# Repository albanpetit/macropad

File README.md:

# Makerpad

A fully open-source macropad built from scratch — custom PCB, 3D-printed enclosure, and embedded firmware. 20 programmable keys, two rotary encoders, a 2" color display driven by LVGL, and 22 addressable RGB LEDs, all running on an RP2040.

Everything is designed to be reproducible: order the PCB, print the case, flash the firmware, and configure your keymap via a JSON file.

---

## What's inside

| Directory | Description |
|---|---|
| [`ecad/`](ecad/README.md) | KiCad schematic + PCB, BOM, custom footprints |
| [`mcad/`](mcad/README.md) | STEP files for the enclosure |
| [`fw/`](fw/README.md) | PlatformIO firmware (C++, RP2040) |
| `doc/` | Datasheets, iBOM, schematic PDF |

---

## Hardware at a glance

| Component | Part |
|---|---|
| MCU | RP2040 (LQFN-56), 133 MHz, 264 KB RAM |
| Flash | W25Q128JVP — 16 MB SPI |
| Display | HS20HS072RX — 2" 240×320 ST7789V2-HSD SPI |
| RGB LEDs | WS2812B-2020 × 22 — addressable, 5V |
| Keys | 4 cols × 5 rows = 20 keys |
| Encoders | PEC12R-4225F-S0024 × 2 — 24 PPR + push |
| Connectivity | USB-C (HID keyboard + consumer control) |

---

## Roadmap

- [x] Layer switching via encoder
- [x] Volume control with speaker/mic toggle
- [ ] Macro sequence support
- [ ] Per-key LED color from config
- [ ] OTA config update via USB mass storage

---

## Contributing

See [CONTRIBUTING.md](CONTRIBUTING.md) for the commit convention, scope definitions, and contribution guidelines.

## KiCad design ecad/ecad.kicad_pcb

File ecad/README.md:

# ECAD

PCB design for the Makerpad — schematic and layout done in [KiCad](https://www.kicad.org/).

---

## Files

| File / Directory | Description |
|---|---|
| `ecad.kicad_pro` | KiCad project root |
| `ecad.kicad_sch` | Top-level schematic |
| `switches.kicad_sch` | Key matrix sub-sheet |
| `leds.kicad_sch` | LED chain sub-sheet |
| `ecad.kicad_pcb` | PCB layout |
| `library.pretty/` | Custom footprints (RP2040, WS2812B-2020, encoders…) |
| `3d-models/` | STEP files for 3D preview |
| `ecad-backups/` | KiCad auto-backups |

Exported outputs live in `doc/`:

| Output | Description |
|---|---|
| `doc/bom.xlsx` / `bom.pdf` | Bill of materials |
| `doc/schematic.pdf` | Full schematic PDF |
| `doc/ibom/ibom.html` | Interactive BOM (open in browser) |
| `doc/ecad-export/` | Gerbers and drill files |
| `doc/datasheet/` | Datasheets for key components |

---

## Opening the project

```bash
kicad ecad.kicad_pro
```

Requires KiCad 8 or later. All symbols and footprints are embedded or resolved via `sym-lib-table` and `fp-lib-table` — no external library setup needed.

---

## Interactive BOM

Open `doc/ibom/ibom.html` in any browser. Click a component to highlight its position on the board — useful when soldering.

---

## Ordering the PCB

1. Use the Gerbers in `doc/ecad-export/` and upload them to your preferred fabricator (JLCPCB, PCBWay, OSHPark…).
2. Recommended specs: 2-layer, 1.6 mm FR4, HASL or ENIG finish, 0.2 mm min trace/space.
3. Cross-reference the BOM (`doc/bom.xlsx`) for part numbers and quantities.

---

## Custom footprints (`library.pretty/`)

| Footprint | Component |
|---|---|
| `QFN-56-1EP_7x7mm_P0.4mm` | RP2040 |
| `LED_WS2812B-2020_PLCC4_2.0x2.0mm` | WS2812B-2020 RGB LED |
| `Crystal_SMD_Abracon_ABM8G-4Pin_3.2x2.5mm` | 12 MHz crystal |
| `Hirose_FH12-12S-0.5SH` | 0.5 mm FPC connector (display) |
| `PinHeader_2x05_P1.27mm_Vertical_SMD` | SWD debug header |

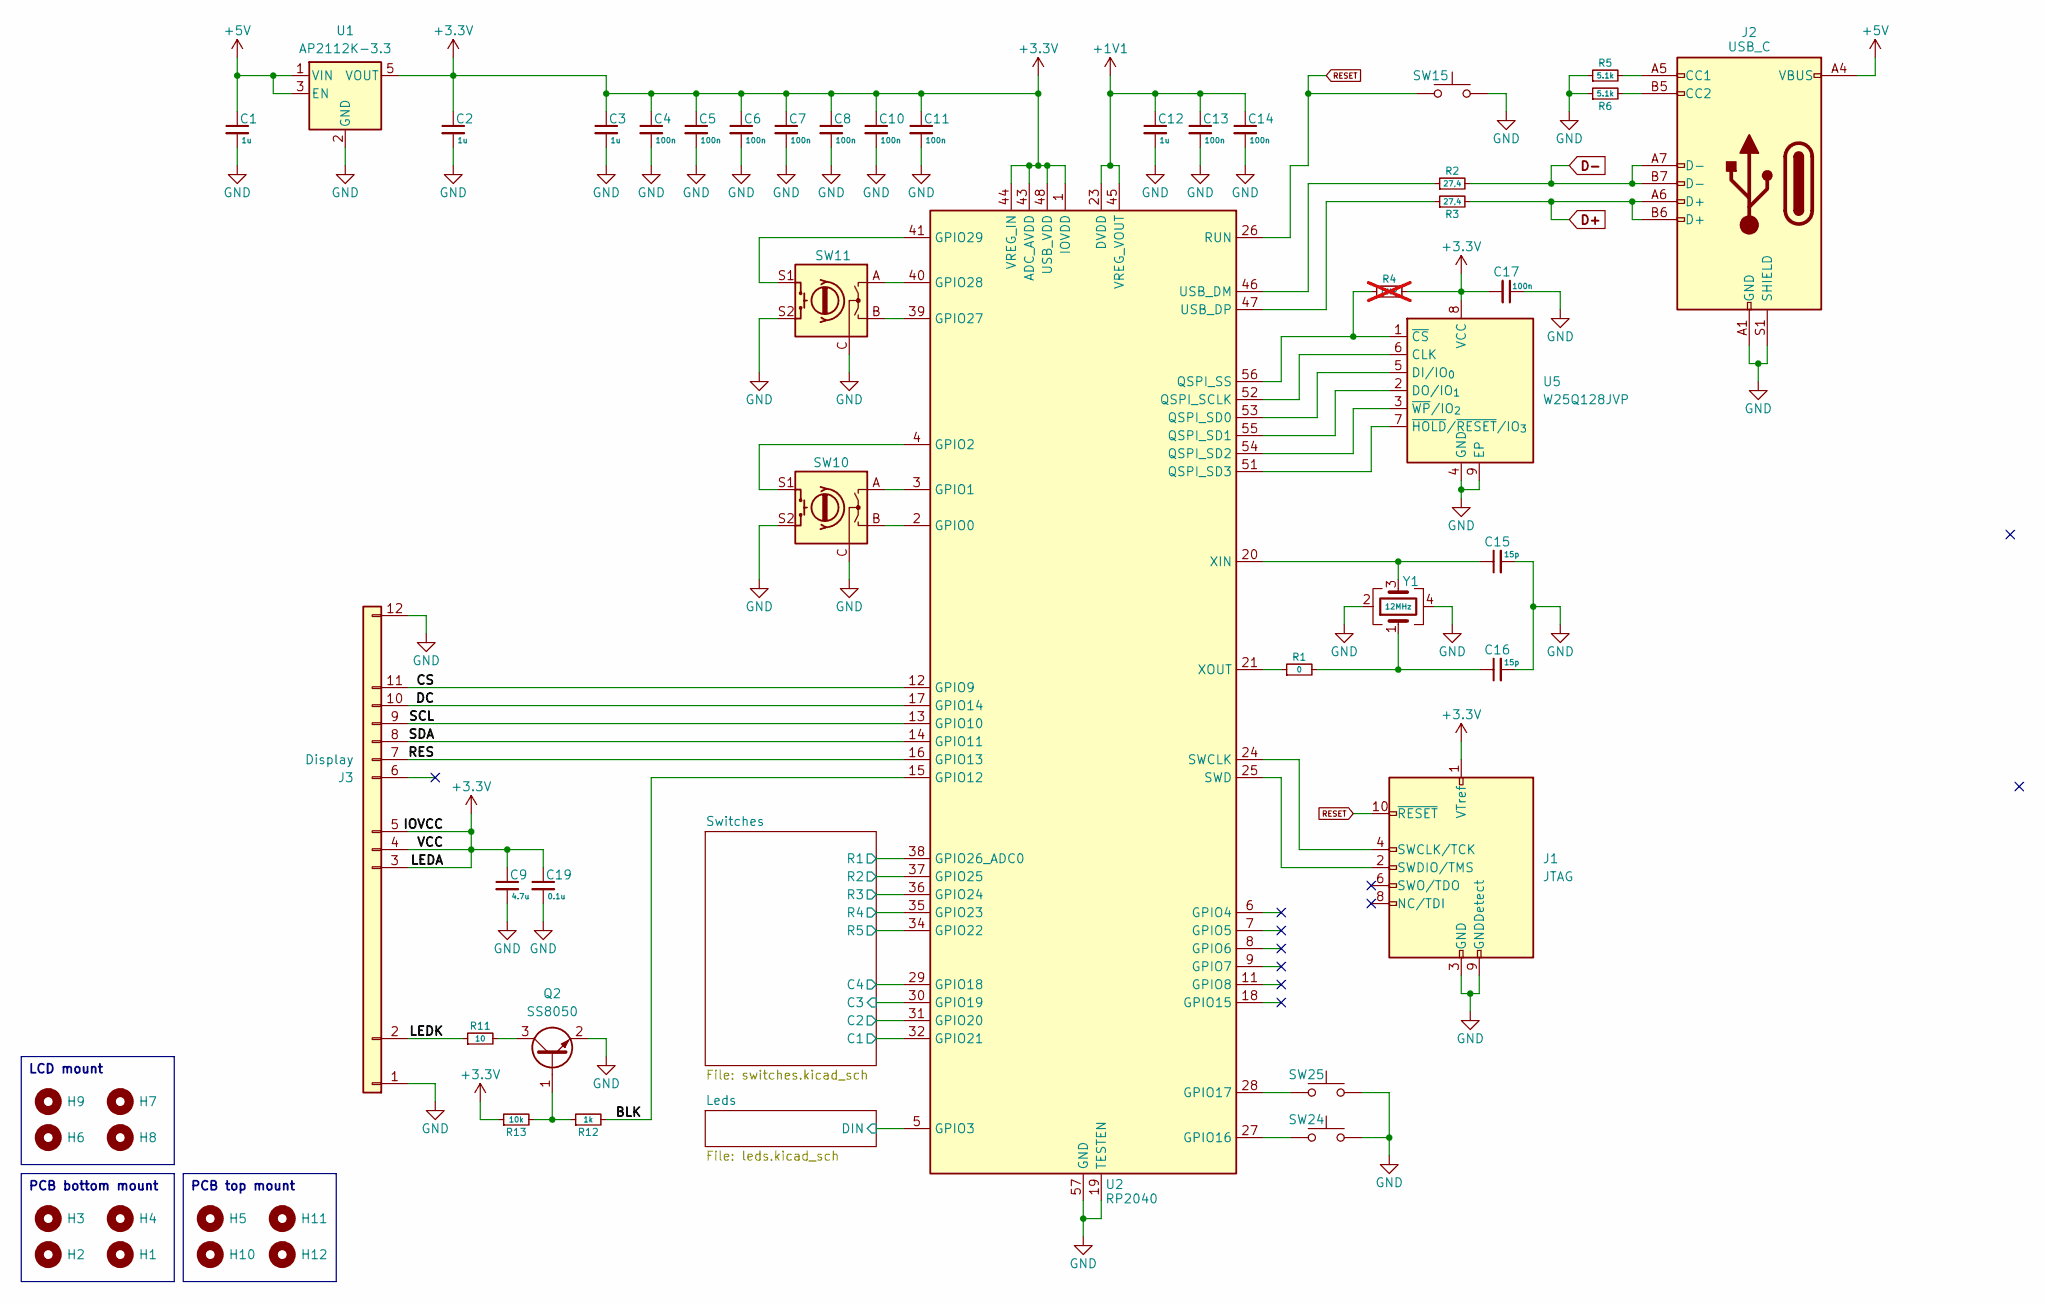
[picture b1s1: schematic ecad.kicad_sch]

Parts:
C1, C2, C3, C12: 1u; C_0402_1005Metric
C4, C5, C6, C7, C8, C10, C11, C13, C14, C17: 100n; C_0402_1005Metric
C9: 4.7u; C_0402_1005Metric
C15, C16: 15p; C_0402_1005Metric
C19: 0.1u; C_0402_1005Metric
H1, H2, H3, H4: MountingHole; smtso3030ctj
H5, H10, H11, H12: MountingHole; MountingHole_3.2mm_M3_DIN965
H6, H7, H8, H9: MountingHole; MountingHole_2.2mm_M2_DIN965
J1: JTAG; PinHeader_2x05_P1.27mm_Vertical_SMD
J2: USB_C; USB_C_Receptacle_Amphenol_12401948E412A
J3: Display; Hirose_FH12-12S-0.5SH_1x12-1MP_P0.50mm_Horizontal
Q2: SS8050; SOT-23
R1: 0; R_0402_1005Metric
R2, R3: 27,4; R_0402_1005Metric
R4: DNP; R_0402_1005Metric; not fitted
R5, R6: 5.1k; R_0402_1005Metric
R11: 10; R_0402_1005Metric
R12: 1k; R_0402_1005Metric
R13: 10k; R_0402_1005Metric
SW10, SW11: RotaryEncoder_Switch; RotaryEncoder_Bourns_Vertical_PEC12R-3x17F-Sxxxx
SW15: RESET; SW_Push_1P1T_NO_CK_KMR2
SW24, SW25: SW_PUSH_6mm
U1: AP2112K-3.3; SOT-23-5
U2: RP2040; QFN-56-1EP_7x7mm_P0.4mm_EP3.2x3.2mm
U5: W25Q128JVP; WSON-8-1EP_6x5mm_P1.27mm_EP3.4x4.3mm
Y1: 12MHz; Crystal_SMD_Abracon_ABM8G-4Pin_3.2x2.5mm

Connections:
+1V1: C12.1, C13.1, C14.1, U2.23 (DVDD), U2.45 (VREG_VOUT), U2.50 (DVDD)
+3.3V: C2.1, C3.1, C4.1, C5.1, C6.1, C7.1, C8.1, C9.1, C10.1, C11.1, C17.2, C19.1, J1.1 (VTref), J3.3, J3.4, J3.5, R4.2, R13.1, U1.5 (VOUT), U2.1 (IOVDD), U2.10 (IOVDD), U2.22 (IOVDD), U2.33 (IOVDD), U2.42 (IOVDD), U2.43 (ADC_AVDD), U2.44 (VREG_IN), U2.48 (USB_VDD), U2.49 (IOVDD), U5.8 (VCC)
+5V: C1.1, J2.A4 (VBUS), J2.A9 (VBUS), J2.B4 (VBUS), J2.B9 (VBUS), U1.1 (VIN), U1.3 (EN); also elsewhere on the board
/BLK: R12.2, U2.15 (GPIO12)
/CS: J3.11, U2.12 (GPIO9)
/DC: J3.10, U2.17 (GPIO14)
/LEDK: J3.2, R11.1
/Leds/DIN: U2.5 (GPIO3); also elsewhere on the board
/RES: J3.7, U2.16 (GPIO13)
/SCL: J3.9, U2.13 (GPIO10)
/SDA: J3.8, U2.14 (GPIO11)
/Switches/C1: U2.32 (GPIO21); also elsewhere on the board
/Switches/C2: U2.31 (GPIO20); also elsewhere on the board
/Switches/C3: U2.30 (GPIO19); also elsewhere on the board
/Switches/C4: U2.29 (GPIO18); also elsewhere on the board
/Switches/R1: U2.38 (GPIO26_ADC0); also elsewhere on the board
/Switches/R2: U2.37 (GPIO25); also elsewhere on the board
/Switches/R3: U2.36 (GPIO24); also elsewhere on the board
/Switches/R4: U2.35 (GPIO23); also elsewhere on the board
/Switches/R5: U2.34 (GPIO22); also elsewhere on the board
D+: J2.A6 (D+), J2.B6 (D+), R3.2
D-: J2.A7 (D-), J2.B7 (D-), R2.2
GND: C1.2, C2.2, C3.2, C4.2, C5.2, C6.2, C7.2, C8.2, C9.2, C10.2, C11.2, C12.2, C13.2, C14.2, C15.2, C16.2, C17.1, C19.2, J1.3 (GND), J1.5 (GND), J1.9 (GNDDetect), J2.A1 (GND), J2.A12 (GND), J2.B1 (GND), J2.B12 (GND), J2.S1 (SHIELD), J3.1, J3.12, Q2.2 (E), R5.1, R6.1, SW10.C, SW10.S2, SW11.C, SW11.S2, SW15.2, SW24.2, SW25.2, U1.2 (GND), U2.19 (TESTEN), U2.57 (GND), U5.4 (GND), U5.9 (EP), Y1.2, Y1.4; also elsewhere on the board
unnamed: C16.1, R1.2, Y1.1
unnamed: J1.4 (SWCLK/TCK), U2.24 (SWCLK)
unnamed: J1.2 (SWDIO/TMS), U2.25 (SWD)
unnamed: J2.A5 (CC1), R5.2
unnamed: J2.B5 (CC2), R6.2
unnamed: Q2.1 (B), R12.1, R13.2
unnamed: Q2.3 (C), R11.2
unnamed: SW10.B, U2.2 (GPIO0)
unnamed: SW10.A, U2.3 (GPIO1)
unnamed: SW10.S1, U2.4 (GPIO2)
unnamed: SW24.1, U2.27 (GPIO16)
unnamed: SW25.1, U2.28 (GPIO17)
unnamed: SW11.B, U2.39 (GPIO27)
unnamed: SW11.A, U2.40 (GPIO28)
unnamed: SW11.S1, U2.41 (GPIO29)
unnamed: U2.52 (QSPI_SCLK), U5.6 (CLK)
unnamed: U2.53 (QSPI_SD0), U5.5 (DI/IO_{0})
unnamed: U2.55 (QSPI_SD1), U5.2 (DO/IO_{1})
unnamed: U2.54 (QSPI_SD2), U5.3 (~WP/IO_{2})
unnamed: U2.51 (QSPI_SD3), U5.7 (~HOLD/~RESET/IO_{3})
unnamed: R4.1, U2.56 (QSPI_SS), U5.1 (~CS)
unnamed: R2.1, U2.46 (USB_DM)
unnamed: R3.1, U2.47 (USB_DP)
unnamed: C15.1, U2.20 (XIN), Y1.3
unnamed: R1.1, U2.21 (XOUT)
RESET: J1.10 (~RESET), SW15.1, U2.26 (RUN)

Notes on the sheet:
LCD mount
PCB bottom mount
PCB top mount

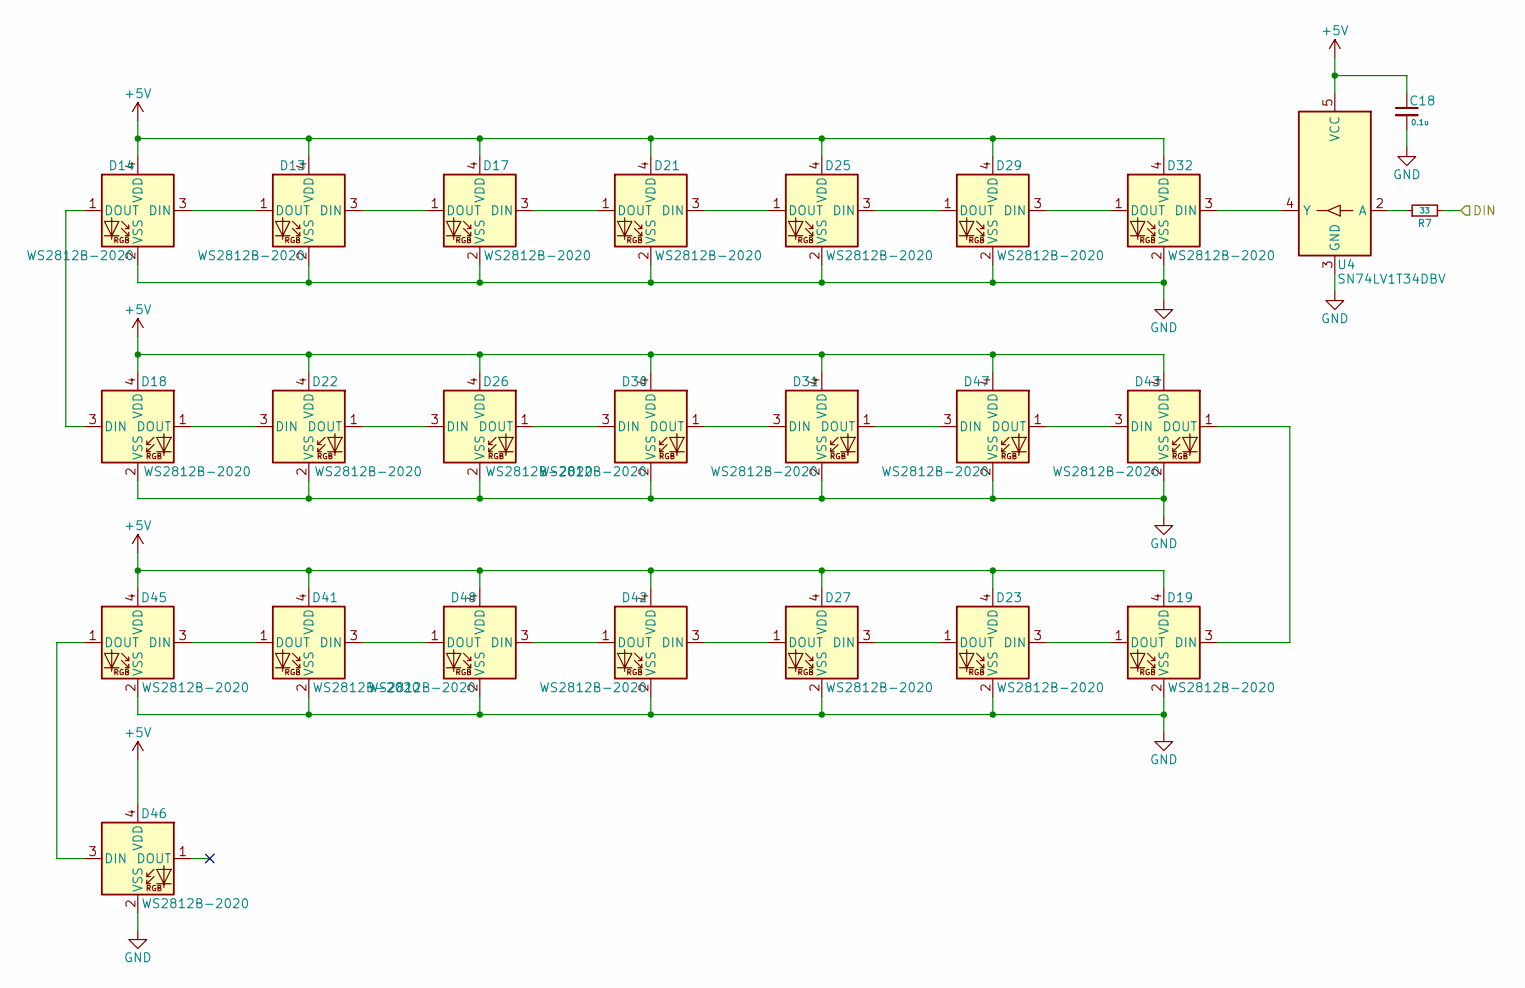
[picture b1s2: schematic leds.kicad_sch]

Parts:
C18: 0.1u; C_0402_1005Metric
D13, D14, D17, D18, D19, D21, D22, D23, D25, D26, D27, D29, D30, D31, D32, D41, D42, D43, D45, D46, D47, D48: WS2812B-2020; LED_WS2812B-2020_PLCC4_2.0x2.0mm
R7: 33; R_0402_1005Metric
U4: SN74LV1T34DBV; SOT-23-5

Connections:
+5V: C18.1, D13.4 (VDD), D14.4 (VDD), D17.4 (VDD), D18.4 (VDD), D19.4 (VDD), D21.4 (VDD), D22.4 (VDD), D23.4 (VDD), D25.4 (VDD), D26.4 (VDD), D27.4 (VDD), D29.4 (VDD), D30.4 (VDD), D31.4 (VDD), D32.4 (VDD), D41.4 (VDD), D42.4 (VDD), D43.4 (VDD), D45.4 (VDD), D46.4 (VDD), D47.4 (VDD), D48.4 (VDD), U4.5 (VCC); also elsewhere on the board
/Leds/DIN: R7.2; also elsewhere on the board
GND: C18.2, D13.2 (VSS), D14.2 (VSS), D17.2 (VSS), D18.2 (VSS), D19.2 (VSS), D21.2 (VSS), D22.2 (VSS), D23.2 (VSS), D25.2 (VSS), D26.2 (VSS), D27.2 (VSS), D29.2 (VSS), D30.2 (VSS), D31.2 (VSS), D32.2 (VSS), D41.2 (VSS), D42.2 (VSS), D43.2 (VSS), D45.2 (VSS), D46.2 (VSS), D47.2 (VSS), D48.2 (VSS), U4.3 (GND); also elsewhere on the board
unnamed: D13.3 (DIN), D17.1 (DOUT)
unnamed: D13.1 (DOUT), D14.3 (DIN)
unnamed: D14.1 (DOUT), D18.3 (DIN)
unnamed: D17.3 (DIN), D21.1 (DOUT)
unnamed: D18.1 (DOUT), D22.3 (DIN)
unnamed: D19.3 (DIN), D43.1 (DOUT)
unnamed: D19.1 (DOUT), D23.3 (DIN)
unnamed: D21.3 (DIN), D25.1 (DOUT)
unnamed: D22.1 (DOUT), D26.3 (DIN)
unnamed: D23.1 (DOUT), D27.3 (DIN)
unnamed: D25.3 (DIN), D29.1 (DOUT)
unnamed: D26.1 (DOUT), D30.3 (DIN)
unnamed: D27.1 (DOUT), D42.3 (DIN)
unnamed: D29.3 (DIN), D32.1 (DOUT)
unnamed: D30.1 (DOUT), D31.3 (DIN)
unnamed: D31.1 (DOUT), D47.3 (DIN)
unnamed: D32.3 (DIN), U4.4 (Y)
unnamed: D41.3 (DIN), D48.1 (DOUT)
unnamed: D41.1 (DOUT), D45.3 (DIN)
unnamed: D42.1 (DOUT), D48.3 (DIN)
unnamed: D43.3 (DIN), D47.1 (DOUT)
unnamed: D45.1 (DOUT), D46.3 (DIN)
unnamed: R7.1, U4.2 (A)

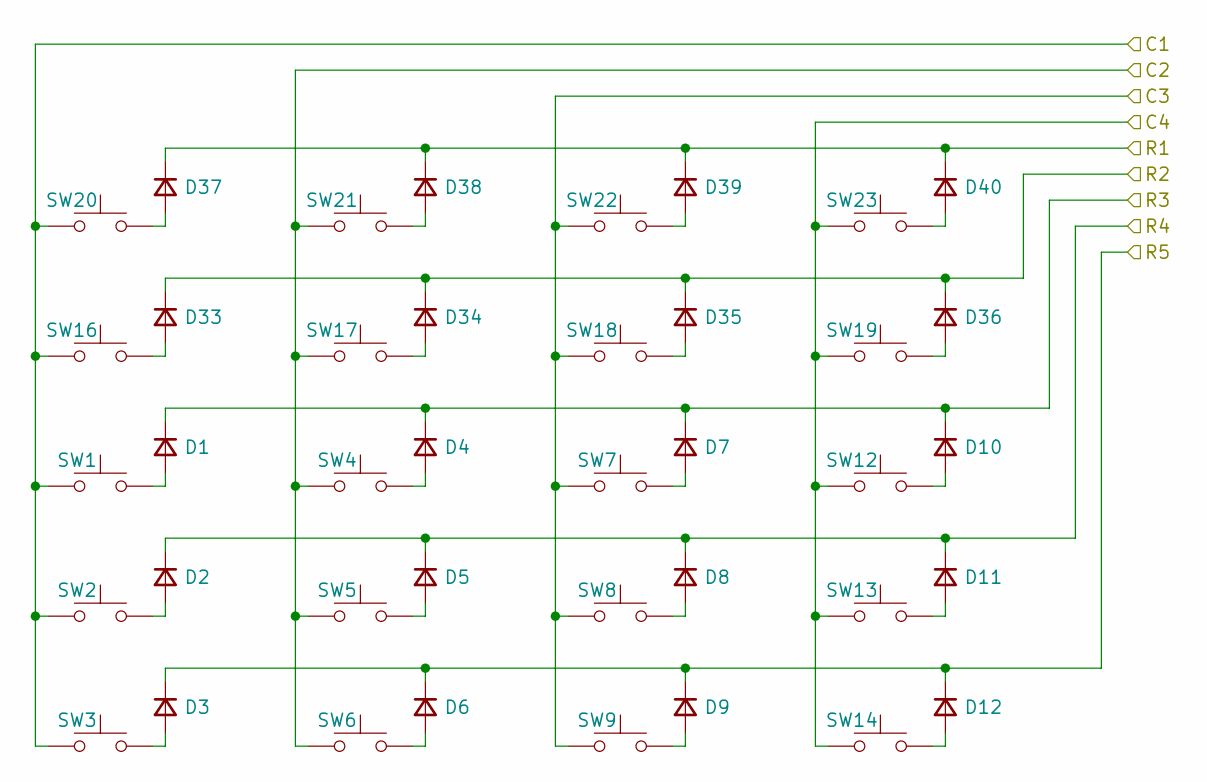
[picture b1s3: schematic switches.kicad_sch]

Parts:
D1, D2, D3, D4, D5, D6, D7, D8, D9, D10, D11, D12, D33, D34, D35, D36, D37, D38, D39, D40: 1N4148W; D_SOD-123
SW1, SW2, SW3, SW4, SW5, SW6, SW7, SW8, SW9, SW12, SW13, SW14, SW16, SW17, SW18, SW19, SW20, SW21, SW22, SW23: Kailh choc v2; SW_Hotswap_Kailh_Choc_V2

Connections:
/Switches/C1: SW1.1, SW2.1, SW3.1, SW16.1, SW20.1; also elsewhere on the board
/Switches/C2: SW4.1, SW5.1, SW6.1, SW17.1, SW21.1; also elsewhere on the board
/Switches/C3: SW7.1, SW8.1, SW9.1, SW18.1, SW22.1; also elsewhere on the board
/Switches/C4: SW12.1, SW13.1, SW14.1, SW19.1, SW23.1; also elsewhere on the board
/Switches/R1: D37.1 (K), D38.1 (K), D39.1 (K), D40.1 (K); also elsewhere on the board
/Switches/R2: D33.1 (K), D34.1 (K), D35.1 (K), D36.1 (K); also elsewhere on the board
/Switches/R3: D1.1 (K), D4.1 (K), D7.1 (K), D10.1 (K); also elsewhere on the board
/Switches/R4: D2.1 (K), D5.1 (K), D8.1 (K), D11.1 (K); also elsewhere on the board
/Switches/R5: D3.1 (K), D6.1 (K), D9.1 (K), D12.1 (K); also elsewhere on the board
unnamed: D1.2 (A), SW1.2
unnamed: D2.2 (A), SW2.2
unnamed: D3.2 (A), SW3.2
unnamed: D4.2 (A), SW4.2
unnamed: D5.2 (A), SW5.2
unnamed: D6.2 (A), SW6.2
unnamed: D7.2 (A), SW7.2
unnamed: D8.2 (A), SW8.2
unnamed: D9.2 (A), SW9.2
unnamed: D10.2 (A), SW12.2
unnamed: D11.2 (A), SW13.2
unnamed: D12.2 (A), SW14.2
unnamed: D33.2 (A), SW16.2
unnamed: D34.2 (A), SW17.2
unnamed: D35.2 (A), SW18.2
unnamed: D36.2 (A), SW19.2
unnamed: D37.2 (A), SW20.2
unnamed: D38.2 (A), SW21.2
unnamed: D39.2 (A), SW22.2
unnamed: D40.2 (A), SW23.2

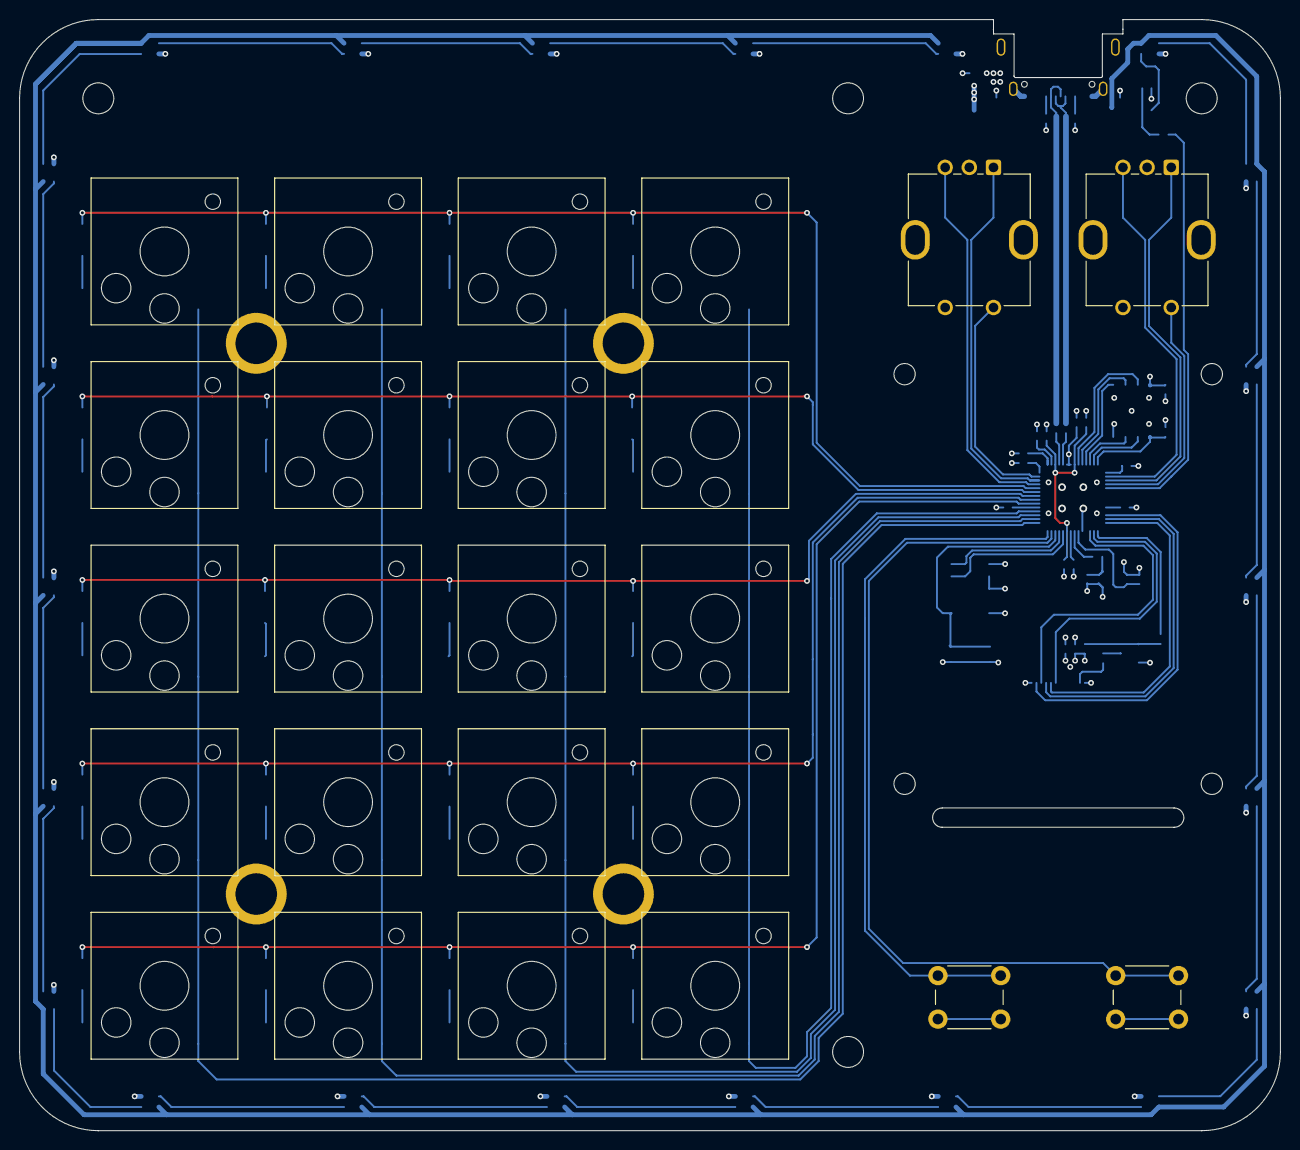
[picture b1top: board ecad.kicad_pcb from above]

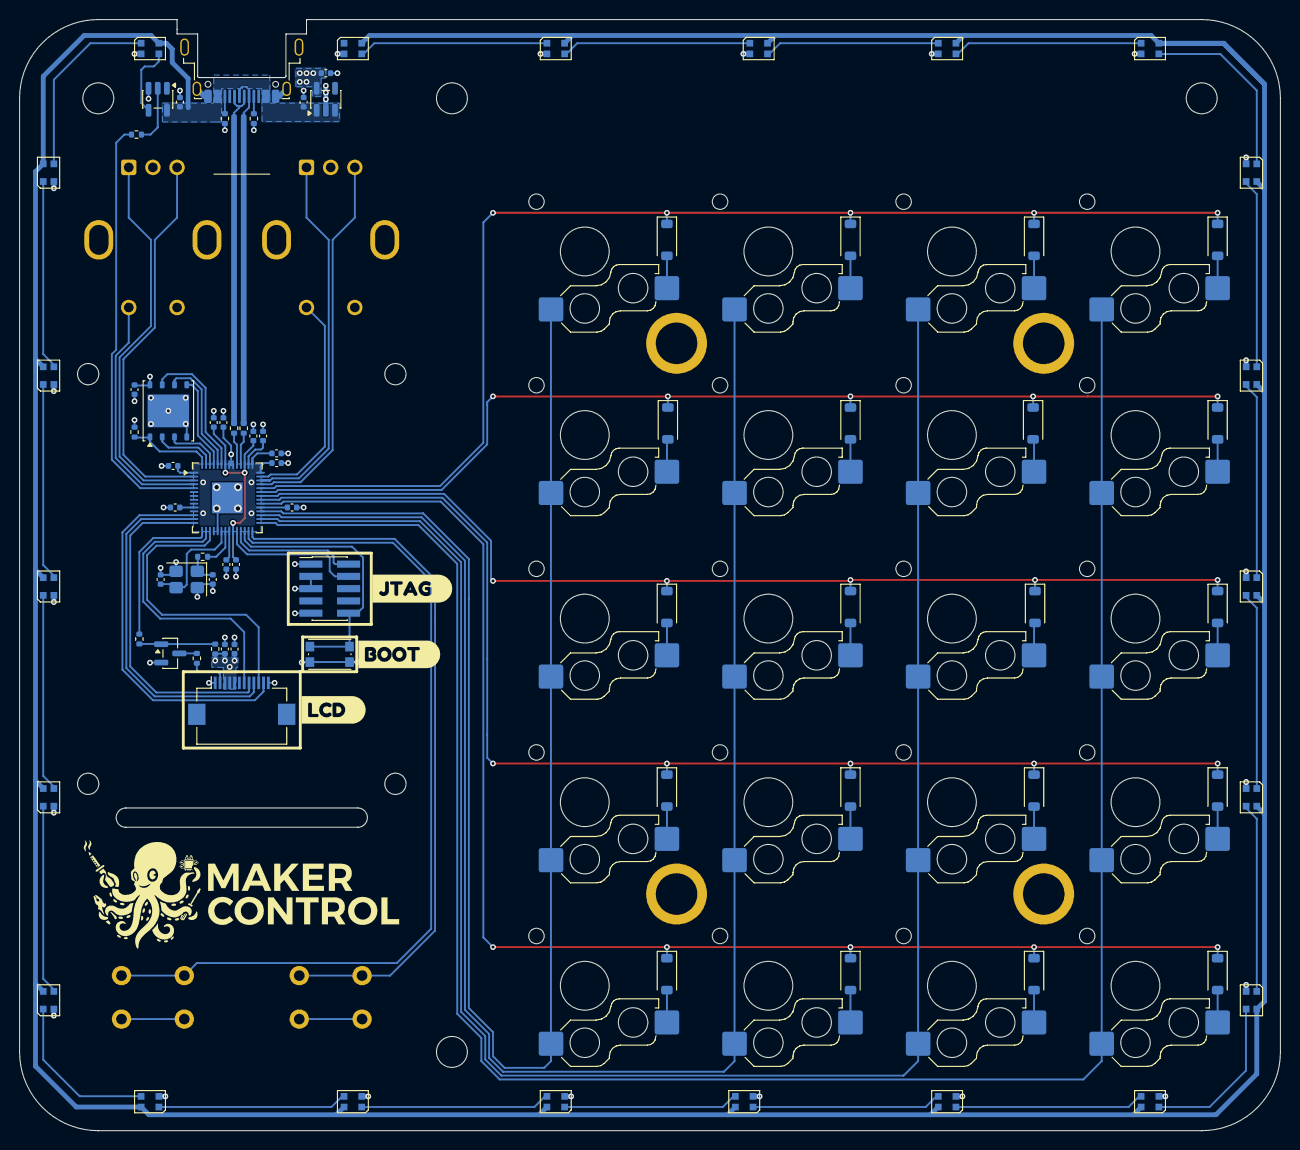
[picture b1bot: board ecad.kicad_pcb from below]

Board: 4 copper layers, 130.5 x 115.0 mm, 120 parts (88 on the bottom side), 92 nets.

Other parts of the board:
kibuzzard-68D988DF: G***; kibuzzard-68D988DF
kibuzzard-68D9895D: G***; kibuzzard-68D9895D
kibuzzard-68D98929: G***; kibuzzard-68D98929

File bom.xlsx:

Electronic BOM
Reference | Qty | Value | Mrf# | LCSC part # | Footprint | Datasheet
C1,C2,C3,C12 | 4 | 1u | GRM155R61H105KE05D | C1518208 | Capacitor_SMD:C_0402_1005Metric | ~
C4,C5,C6,C7,C8,C10,C11,C13,C14,C17 | 10 | 100n | GRM155R71H104KE14D | C77020 | Capacitor_SMD:C_0402_1005Metric | ~
C9 | 1 | 4.7u | GCM1555C1H4R7CA16J | C2191748 | Capacitor_SMD:C_0402_1005Metric | ~
C15,C16 | 2 | 15p | GJM1555C1H150FB01D | C441742 | Capacitor_SMD:C_0402_1005Metric | ~
C18,C19 | 2 | 0.1u |  | C77020 | Capacitor_SMD:C_0402_1005Metric | ~
D1,D2,D3,D4,D5,D6,D7,D8,D9,D10,D11,D12,D33,D34,D35,D36,D37,D38,D39,D40 | 20 | 1N4148W | 1N4148W-E3-08 | C241939 | Diode_SMD:D_SOD-123 | ~
D13,D14,D17,D18,D19,D21,D22,D23,D25,D26,D27,D29,D30,D31,D32,D41,D42,D43,D45,D46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 | 22 | WS2812B-2020 | WS2812B-2020 | C965555 | LED_SMD:LED_WS2812B-2020_PLCC4_2.0x2.0mm | https://cdn-shop.adafruit.com/product-files/4684/4684_WS2812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
H1,H2,H3,H4 | 4 | MountingHole | SMTSO3030CTJ | C2915308 | Mounting_Wuerth:Mounting_Wuerth_WA-SMSI-M3_H4mm_9774040360 | ~
H5,H10,H11,H12 | 4 | MountingHole |  | ~ | MountingHole:MountingHole_3.2mm_M3_DIN965 | ~
H6,H7,H8,H9 | 4 | MountingHole |  | ~ | MountingHole:MountingHole_2.2mm_M2_DIN965 | ~
J1 | 1 | JTAG | HX PZ1.27-2x5P TP | C41376037 | Connector_PinHeader_1.27mm:PinHeader_2x05_P1.27mm_Vertical_SMD | http://infocenter.arm.com/help/topic/com.arm.doc.ddi0314h/DD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
J2 | 1 | USB_C | 12401948E412A | C3197899 | Connector_USB:USB_C_Receptacle_Amphenol_12401948E412A | https://www.usb.org/sites/default/files/documents/usb_type-c.zip
J3 | 1 | Display | FH12-12S-0.5SH(55) | C88360 | Connector_FFC-FPC:Hirose_FH12-12S-0.5SH_1x12-1MP_P0.50mm_Horizontal | ~
Q2 | 1 | SS8050 | SS8050 | C2914407 | Package_TO_SOT_SMD:SOT-23 | http://www.secosgmbh.com/datasheet/products/SSMPTransistor/S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
R1,R4,R13 | 3 | 10k | RC0402FR-0710KL | C60490 | Resistor_SMD:R_0402_1005Metric | ~
R2,R3,R5,R6 | 4 | 27.4 | RC0402FR-0727R4L | C274349 | Resistor_SMD:R_0402_1005Metric | ~
R7 | 1 | 33 | RC0402FR-0733RL | C138002 | Resistor_SMD:R_0402_1005Metric | ~
R11 | 1 | 10 | AC0402FR-0710RL | C144805 | Resistor_SMD:R_0402_1005Metric | ~
R12 | 1 | 1k | RC0402FR-071KL | C106235 | Resistor_SMD:R_0402_1005Metric | ~
SW1,SW2,SW3,SW4,SW5,SW6,SW7,SW8,SW9,SW12,SW13,SW14,SW16,SW17,SW18,SW19,SW20,SW2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 | 20 | Kailh choc v2 |  |  | PCM_Switch_Keyboard_Hotswap_Kailh:SW_Hotswap_Kailh_Choc_V2 | ~
DISPLAY | 1 | HS HS20HS072RX | HS20HS072RX | C5329582
SW10,SW11 | 2 | RotaryEncoder_Switch | PEC12R-4225F-S0024 | C18164805 | Rotary_Encoder:RotaryEncoder_Bourns_Vertical_PEC12R-3x17F-Sxxxx | ~
SW15 | 1 | RESET | KMR223GLFG | C221678 | Button_Switch_SMD:SW_Push_1P1T_NO_CK_KMR2 | ~
SW24,SW25 | 2 |  | SH-6X6X5.5H-CJ | C42416244 | Button_Switch_THT:SW_PUSH_6mm | ~
U1 | 1 | AP2112K-3.3 | AP2112K-3.3TRG1 | C51118 | Package_TO_SOT_SMD:SOT-23-5 | https://www.diodes.com/assets/Datasheets/AP2112.pdf
U2 | 1 | RP2040 | RP2040 | C2040 | Package_DFN_QFN:QFN-56-1EP_7x7mm_P0.4mm_EP3.2x3.2mm | https://datasheets.raspberrypi.com/rp2040/rp2040-datasheet.pdf
U4 | 1 | SN74LV1T34DBV | SN74LV1T34DBVR | C100024 | Package_TO_SOT_SMD:SOT-23-5 | https://www.ti.com/lit/ds/symlink/sn74lv1t34.pdf
U5 | 1 | W25Q128JVP | W25Q128JVPIQ | C190862 | Package_SON:WSON-8-1EP_6x5mm_P1.27mm_EP3.4x4.3mm | https://www.winbond.com/resource-files/w25q128jv_dtr%20revc%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
Y1 | 1 | 12MHz | ABM8-272-T3 | C20625731 | Crystal:Crystal_SMD_Abracon_ABM8AIG-4Pin_3.2x2.5mm | ~

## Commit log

2025-08-21 init: first commit
2025-09-01 feat(ecad): change pcb size to have constant margin
2025-09-05 doc(feat): add commit convention documentation
2025-09-17 feat(mcad): add step of kailh switch
2025-09-17 feat(mcad): add step of lcd module
2025-09-17 feat(mcad): add dxf of the lcd module to guide pcb design
2025-09-18 fix(ecad): change pcb format
2025-09-21 fix(ecad): replace components to fit new format
2025-09-22 fix(mcad): remove lcd-module files to replace by a non breakout tft screen
2025-09-22 feat(ecad): add buttons, fpc connector, and holes to pass flexible pcb of display
2025-09-22 doc(ecad): add fpc connector datasheet and catalog
2025-09-24 feat(ecad): hierarchical sheets, add switches net and change some components placement
2025-09-24 doc(ecad): add display datasheet and use case datasheet
2025-09-25 feat(ecad): route rotary encoders and change some pins arrangement
2025-09-26 feat(ecad): change ref of swtiche diode and make the circuitry for the display
2025-09-28 doc(ecad): remove bad datasheet
2025-09-28 feat(ecad): general routing
2025-10-08 fix(ecad): change screw placement and rounded corners
2025-10-09 feat(ecad): ws2812b placement and routing
2025-10-12 feat(ecad): gerber update
2025-10-12 doc(ecad): add rp2040 datasheet
2025-10-12 doc(ecad): add folder for pdf export of schematic and pcb
2025-10-12 fix(ecad): change usb connector
2025-10-12 dov(ecad): add usb connector datasheet
2025-10-12 feat(ecad): add missing 3d files to render pcb
2025-10-12 fix(ecad): change screw holes size
2025-10-12 chore(repo): gitignore all zip files
2025-11-06 doc(ecad): add encoders datasheet
2025-11-06 fix(ecad): change pcb dimensions
2025-11-12 fix(ecad): change board dimensions
2025-11-12 feat(mcad): export new ecad 3d file
2025-11-12 feat(doc): add bom files
2025-11-12 feat(doc): add crystal datasheet and pcb nuts datasheet
2025-11-12 feat(ecad): add pcb nuts on pcb
2025-11-13 feat(doc): add 6x6 buttons datasheet and change datasheet name of pcbnuts
2025-11-13 feat(doc): reference all components with lcsc in bom files
2025-11-17 feat(ecad): add graphic logo to pcb
2025-11-18 fix(doc): remove useless bom and replace it with new one
2025-11-18 fix(doc): update bom in pdf
2025-11-19 feat(ecad): update gerber to latest version of pcb
2025-11-22 chore(doc): change documentation structure in a specific folder
2026-05-18 feat(fw): scaffold firmware with LVGL, HID, matrix and LED support
    Add complete firmware base for the RP2040 macropad:
    - PlatformIO project (earlephilhower core, TFT_eSPI, LVGL 8.3, ArduinoJson)
    - HAL modules: key matrix 4×5, rotary encoder, WS2812B LEDs, ST7789 display
    - USB HID via arduino-pico native Keyboard (standard + consumer keys)
    - LittleFS + ArduinoJson config storage with 2 default layers
    - LVGL UI scaffold: home screen and settings screen
2026-05-18 feat(ecad): update schematics and README with hardware documentation
    - Update KiCad schematics (main, LEDs, switches sub-sheets)
    - Update PCB layout
    - Rewrite README with full hardware specs, GPIO map, architecture
    overview, key config format and commit convention
2026-05-21 fix(fw): fix matrix scan direction and switch to USB upload
    - Swap matrix scan direction: rows=OUTPUT strobe, cols=INPUT_PULLUP
    (hardware wired opposite to standard convention)
    - Remove TiGard SWD upload config, USB CDC now working via picotool
    - Update CLAUDE.md to reflect USB-only workflow and document
    matrix scan inversion as a known hardware v1 quirk
    - Clean up main.cpp debug heartbeat code left from matrix diagnosis
2026-05-21 feat(fw): replace potentiometers with encoders and add volume control
    - Replace PIN_POT_* with PIN_ENC0_*/PIN_ENC1_* in config.h
    - Refactor Encoder class to support multiple instances via static
    ISR dispatch table (up to 3 encoders)
    - Add encoder1 (GPIO27/28/29) mapped to HID consumer volume+/volume-
    and mute on button press
    - encoder0 (GPIO16/17/2) remains navigation/UI encoder
2026-05-21 fix(ecad): change sur resistor and capacitor value to ajust
2026-05-21 feat(doc): ibom creation
2026-06-14 refactor(ecad): reorganize footprint library and 3D models
    Replace ecad/3d/ with ecad/3d-models/ (updated model files, JAE connector
    removed, Bourns encoder updated). Add ecad/library.pretty/ with all project
    footprints. Remove old sinhoo-smtso3030ctj local lib. Update fp-lib-table.
2026-06-14 fix(ecad): mark R4 as DNP and update zone fill defaults
    R4 set to do-not-place with value corrected to 0.
    Zone fill parameters expanded in project file (thermal relief, hatch, clearance).
2026-06-14 chore(ecad): update PCB layout, refresh STEP export and remove stale gerbers
    Gerber files removed — to be regenerated from updated PCB.
    New MCAD STEP export replaces ecad-export.step.
2026-06-14 fix(fw): replace TFT_eSPI with raw Pico SDK SPI driver for ST7789V2-HSD
    Complete rewrite of display driver using pico-sdk spi_write_blocking (polling,
    no DMA). Custom ST7789V2-HSD init sequence with INVON. Switch to portrait mode
    240x320. SPI frequency reduced to 15 MHz native. TFT_MISO=-1 to avoid pin
    conflict. Filesystem size set to 0.5 MB.
2026-06-14 feat(fw): add speaker/mic toggle on enc1 long press and redesign UI layer list
    Encoder 1 long press (600ms) toggles between speaker and mic mode, LEDs
    indicate the active mode. Short press mutes the active device.
    UI replaced with a single-screen layer list: header with active layer name,
    scrollable list with color band and active indicator per layer, footer with
    navigation hints. layerChanged() replaces onLayerChanged() callback. Layer
    switch via encoder press syncs LEDs and persists config.
2026-06-14 chore: ignore ecad/.history/ and archive_3d_models.log
2026-06-14 doc: simplify and update README
    Remove verbose GPIO map, commit convention and contributing sections.
    Fix display spec (240x320 portrait, ST7789V2-HSD), replace ADC pot GPIO
    entries with encoder 1 pins, update architecture tree, fix flash commands
    (pico env only). Add Controls section for encoder behaviour. Update roadmap.
2026-06-14 doc: add CONTRIBUTING.md with commit convention and guidelines
2026-06-14 doc: rewrite root README and add ecad/mcad READMEs
2026-06-14 doc: add fw/README and slim down firmware section in root README
